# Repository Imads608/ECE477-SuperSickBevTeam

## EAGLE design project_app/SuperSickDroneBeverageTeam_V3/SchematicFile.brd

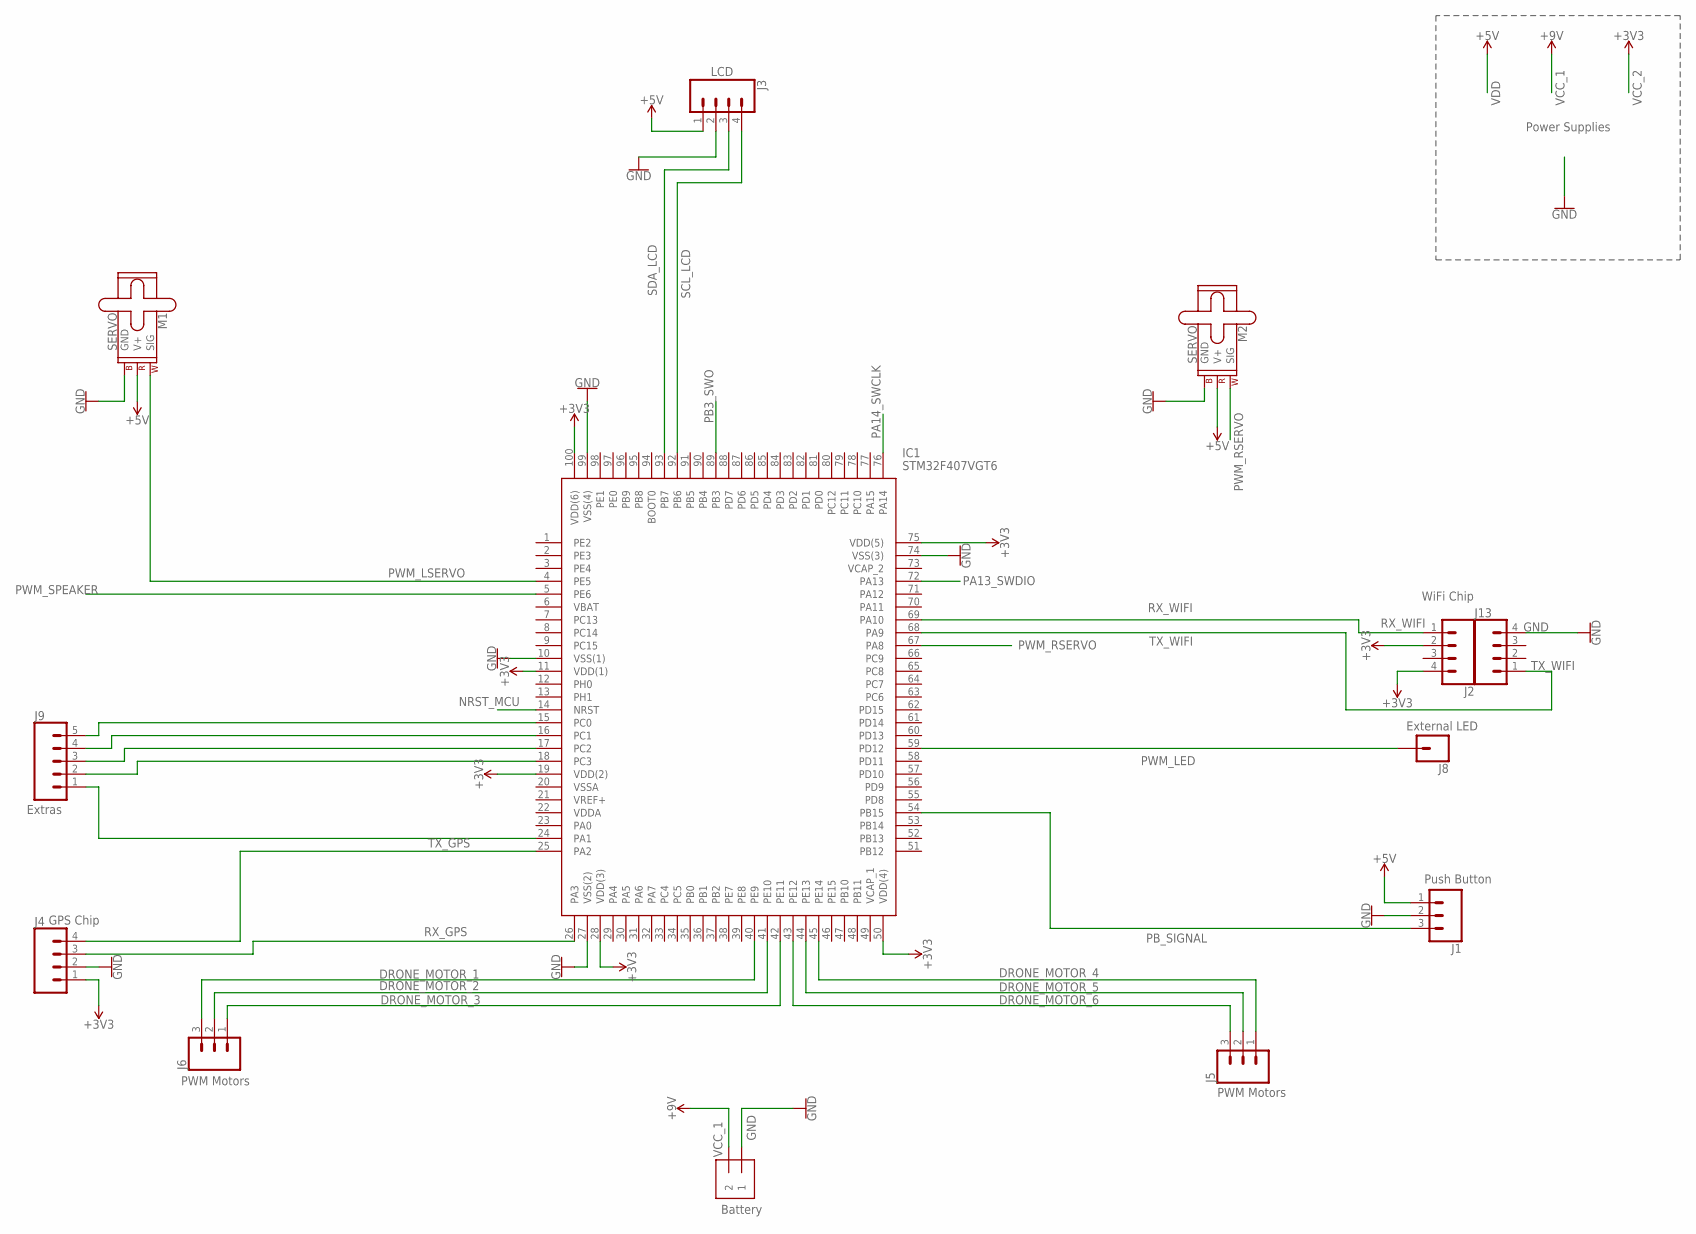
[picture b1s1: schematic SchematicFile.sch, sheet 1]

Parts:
IC1: STM32F407VGT6; QFP50P1600X1600X160-100N
J1, J5, J6: CONN_03; 1X03
J2, J3, J4, J13: CONN_04; 1X04
J8: CONN_01; 1X01
J9: CONN_05; 1X05
J11: 1X2-3.5MM
M1, M2: SERVO; 1X03

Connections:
DRONE_MOTOR_1: IC1.40 (PE9), J6.3
DRONE_MOTOR_2: IC1.41 (PE10), J6.2
DRONE_MOTOR_3: IC1.42 (PE11), J6.1
DRONE_MOTOR_4: IC1.45 (PE14), J5.1
DRONE_MOTOR_5: IC1.44 (PE13), J5.2
DRONE_MOTOR_6: IC1.43 (PE12), J5.3
GND: IC1.10 (VSS(1)), IC1.27 (VSS(2)), IC1.74 (VSS(3)), IC1.99 (VSS(4)), J1.2, J3.2, J4.2, J11.1, J13.4, M1.3 (GND), M2.3 (GND); also elsewhere on the board
NRST_MCU: IC1.14 (NRST); also elsewhere on the board
PA1_EXT: IC1.24 (PA1), J9.1
PA13_SWDIO: IC1.72 (PA13); also elsewhere on the board
PA14_SWCLK: IC1.76 (PA14); also elsewhere on the board
PB3_SWO: IC1.89 (PB3); also elsewhere on the board
PB_SIGNAL: IC1.54 (PB15), J1.3
PC0_EXT: IC1.15 (PC0), J9.5
PC1_EXT: IC1.16 (PC1), J9.4
PC2_EXT: IC1.17 (PC2), J9.3
PC3_EXT: IC1.18 (PC3), J9.2
PWM_LED: IC1.59 (PD12), J8.1
PWM_LSERVO: IC1.4 (PE5), M1.1 (SIG)
PWM_RSERVO: IC1.67 (PA8), M2.1 (SIG)
PWM_SPEAKER: IC1.5 (PE6); also elsewhere on the board
RX_GPS: IC1.26 (PA3), J4.3
RX_WIFI: IC1.69 (PA10), J2.1
SCL_LCD: IC1.92 (PB6), J3.4
SDA_LCD: IC1.93 (PB7), J3.3
TX_GPS: IC1.25 (PA2), J4.4
TX_WIFI: IC1.68 (PA9), J13.1
VCC_1: J11.2; also elsewhere on the board
VCC_2: IC1.11 (VDD(1)), IC1.19 (VDD(2)), IC1.28 (VDD(3)), IC1.50 (VDD(4)), IC1.75 (VDD(5)), IC1.100 (VDD(6)), J2.2, J2.4, J4.1; also elsewhere on the board
VDD: J1.1, J3.1, M1.2 (V+), M2.2 (V+); also elsewhere on the board

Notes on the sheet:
WiFi Chip
LCD
GPS Chip
PWM Motors
Push Button
Power Supplies
External LED
Extras
Battery

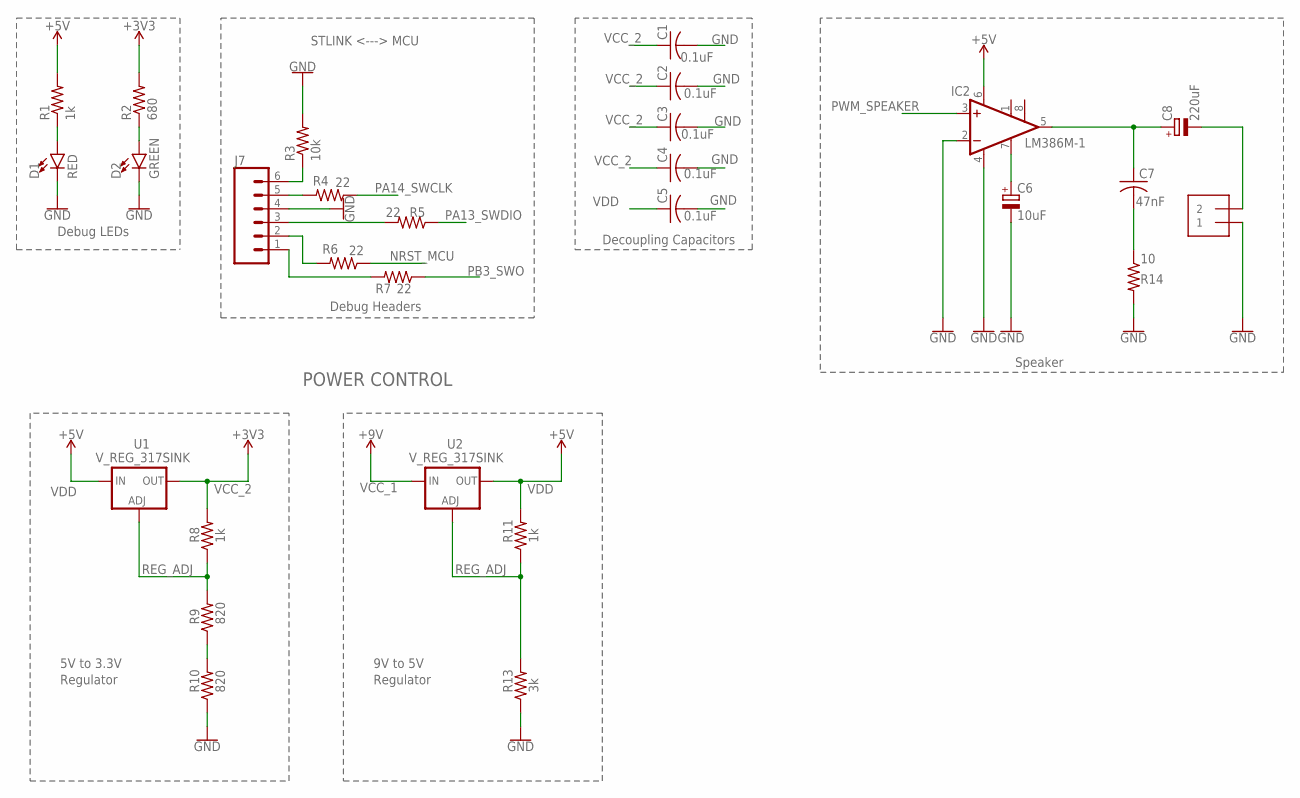
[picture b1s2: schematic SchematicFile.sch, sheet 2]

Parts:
C1, C2, C3, C4, C5: 0.1uF; C0805
C6: 10uF; E2,5-5
C7: 47nF; C0805
C8: 220uF; E2,5-5
D1: RED; LED-1206
D2: GREEN; LED-1206
IC2: LM386M-1; SO08
J7: CONN_06SILK_FEMALE_PTH; 1X06
J12: 1X2-3.5MM
R1, R8, R11: 1k; R0805
R2: 680; R0805
R3: 10k; R0805
R4, R5, R6, R7: 22; R0805
R9, R10: 820; R0805
R13: 3k; R0805
R14: 10; R0805
U1, U2: V_REG_317SINK; TO220-ADJ

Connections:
AUDIO_OUT: C8.-, J12.2
GND: C1.2, C2.2, C3.2, C4.2, C5.2, C6.-, D1.C, D2.C, IC2.2 (-IN), IC2.4 (GND), J7.4, J12.1, R3.2, R10.1, R13.1, R14.2; also elsewhere on the board
GND_STLNK: J7.6, R3.1
unnamed: D1.A, R1.1
unnamed: D2.A, R2.1
unnamed: C6.+, IC2.7 (BYPASS)
unnamed: C7.1, C8.+, IC2.5 (OUT)
unnamed: C7.2, R14.1
unnamed: R9.1, R10.2
NRST_MCU: R6.1; also elsewhere on the board
NRST_STLNK: J7.2, R6.2
PA13_SWDIO: R5.1; also elsewhere on the board
PA14_SWCLK: R4.1; also elsewhere on the board
PB3_SWO: R7.1; also elsewhere on the board
PWM_SPEAKER: IC2.3 (+IN); also elsewhere on the board
REG_ADJ: R8.1, R9.2, R11.1, R13.2, U1.ADJ, U2.ADJ
SWCLK: J7.5, R4.2
SWDIO: J7.3, R5.2
SWO: J7.1, R7.2
VCC_1: U2.IN; also elsewhere on the board
VCC_2: C1.1, C2.1, C3.1, C4.1, R2.2, R8.2, U1.OUT; also elsewhere on the board
VDD: C5.1, IC2.6 (VS), R1.2, R11.2, U1.IN, U2.OUT; also elsewhere on the board

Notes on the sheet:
Debug LEDs
Debug Headers
STLINK <---> MCU
Decoupling Capacitors
POWER CONTROL
5V to 3.3V
Regulator
9V to 5V
Speaker

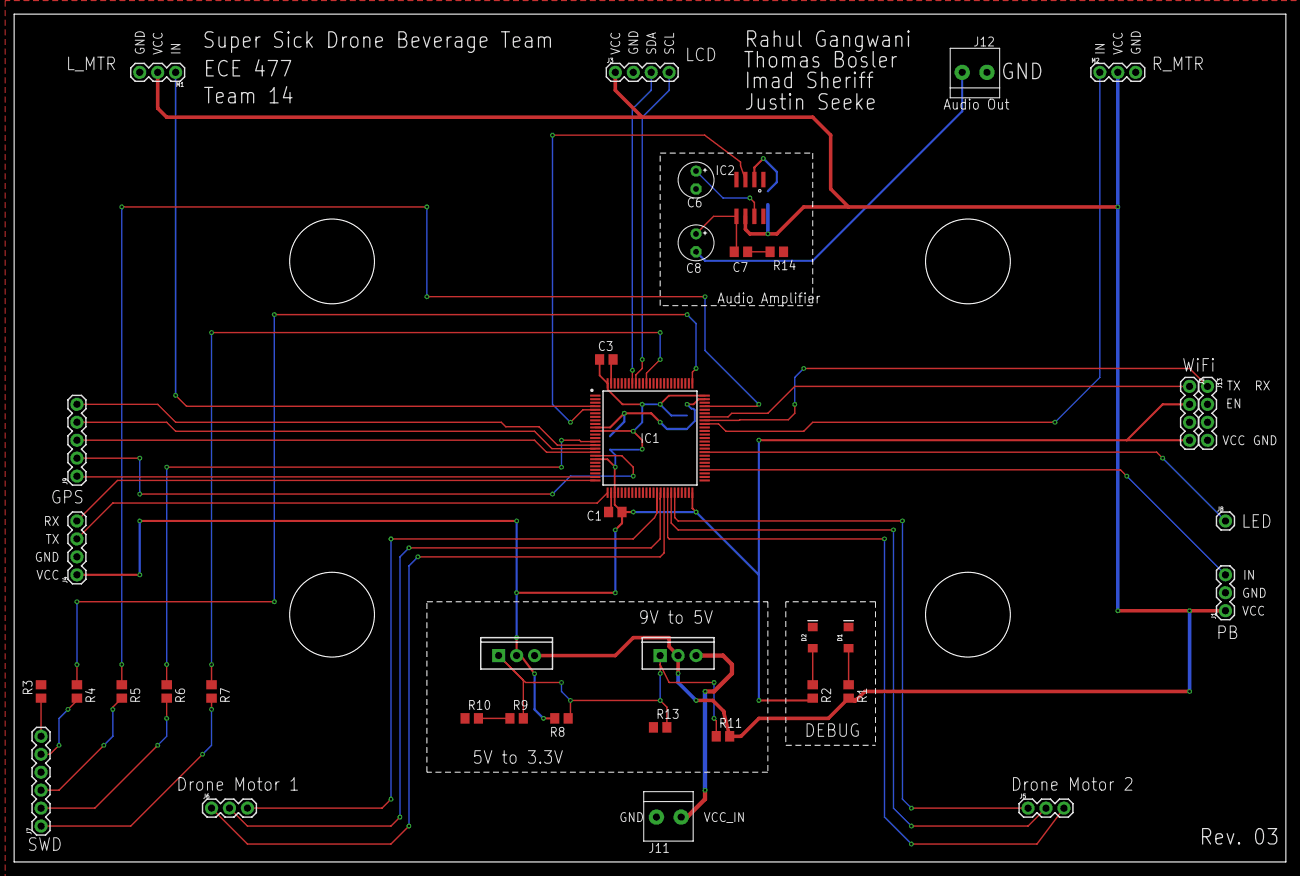
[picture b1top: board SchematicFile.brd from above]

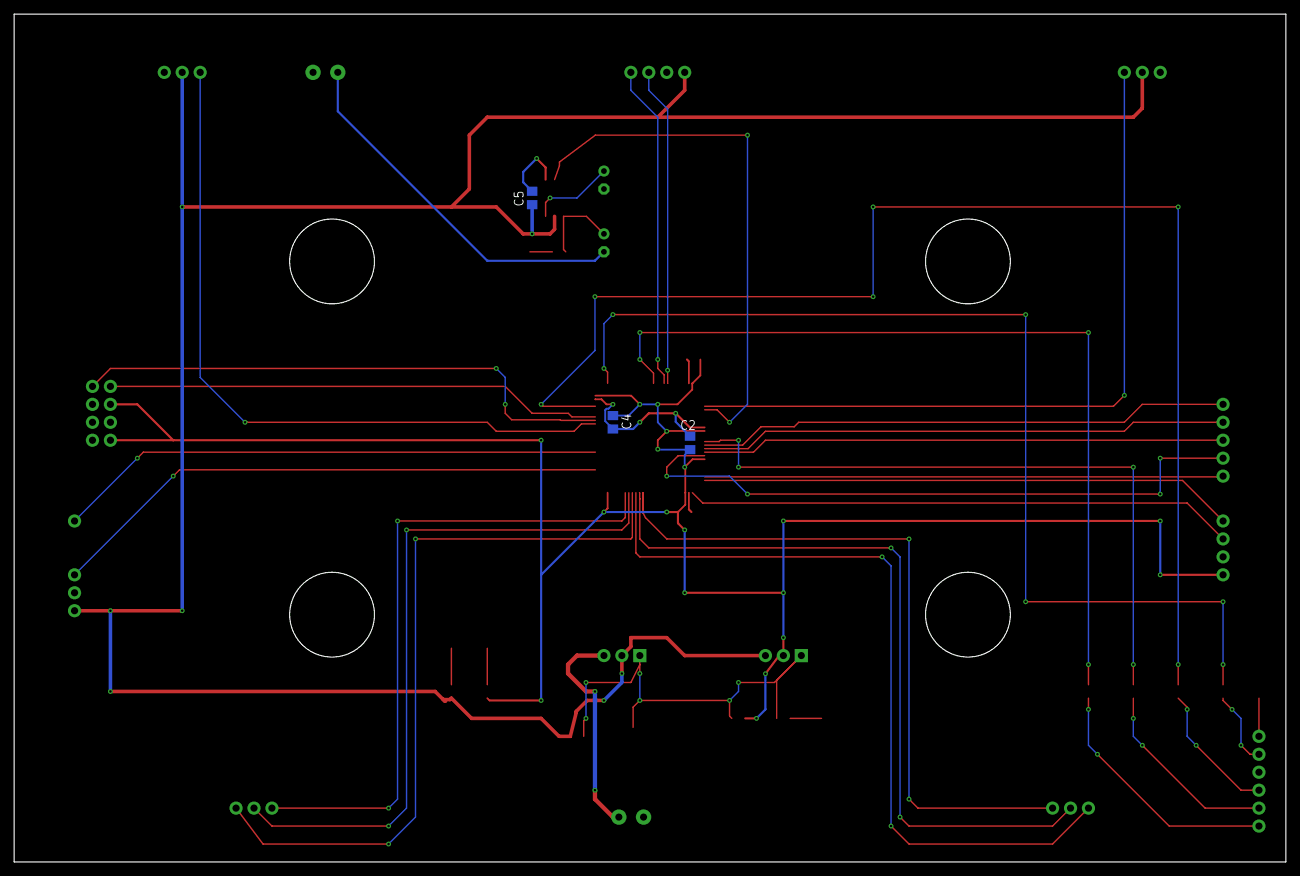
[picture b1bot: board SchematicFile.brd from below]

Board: 2 copper layers, 180.0 x 120.0 mm, 41 parts (3 on the bottom side), 43 nets.

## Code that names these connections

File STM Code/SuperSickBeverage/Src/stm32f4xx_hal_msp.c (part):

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  /* USER CODE END I2C1_MspInit 0 */
  
    /**I2C1 GPIO Configuration    
    PB6     ------> I2C1_SCL
    PB7     ------> I2C1_SDA 
    */
    GPIO_InitStruct.Pin = GPIO_PIN_6|GPIO_PIN_7;
    GPIO_InitStruct.Mode = GPIO_MODE_AF_OD;
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    __HAL_RCC_I2C1_CLK_DISABLE();
  
    /**I2C1 GPIO Configuration    
    PB6     ------> I2C1_SCL
    PB7     ------> I2C1_SDA 
    */
    HAL_GPIO_DeInit(GPIOB, GPIO_PIN_6|GPIO_PIN_7);

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
  /* USER CODE END TIM1_MspPostInit 0 */
    /**TIM1 GPIO Configuration    
    PE11     ------> TIM1_CH2
    PE13     ------> TIM1_CH3
    PE14     ------> TIM1_CH4
    PA8     ------> TIM1_CH1 
    */
    GPIO_InitStruct.Pin = GPIO_PIN_11|GPIO_PIN_13|GPIO_PIN_14;
    GPIO_InitStruct.Mode = GPIO_MODE_AF_PP;
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  /* USER CODE END TIM9_MspPostInit 0 */
  
    /**TIM9 GPIO Configuration    
    PE5     ------> TIM9_CH1
    PE6     ------> TIM9_CH2 
    */
    GPIO_InitStruct.Pin = GPIO_PIN_5|GPIO_PIN_6;
    GPIO_InitStruct.Mode = GPIO_MODE_AF_PP;
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    __HAL_RCC_USART1_CLK_ENABLE();
  
    /**USART1 GPIO Configuration    
    PA9     ------> USART1_TX
    PA10     ------> USART1_RX 
    */
    GPIO_InitStruct.Pin = GPIO_PIN_9|GPIO_PIN_10;
    GPIO_InitStruct.Mode = GPIO_MODE_AF_PP;
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    __HAL_RCC_USART2_CLK_ENABLE();
  
    /**USART2 GPIO Configuration    
    PA2     ------> USART2_TX
    PA3     ------> USART2_RX 
    */
    GPIO_InitStruct.Pin = GPIO_PIN_2|GPIO_PIN_3;
    GPIO_InitStruct.Mode = GPIO_MODE_AF_PP;
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    __HAL_RCC_USART1_CLK_DISABLE();
  
    /**USART1 GPIO Configuration    
    PA9     ------> USART1_TX
    PA10     ------> USART1_RX 
    */
    HAL_GPIO_DeInit(GPIOA, GPIO_PIN_9|GPIO_PIN_10);

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    __HAL_RCC_USART2_CLK_DISABLE();
  
    /**USART2 GPIO Configuration    
    PA2     ------> USART2_TX
    PA3     ------> USART2_RX 
    */
    HAL_GPIO_DeInit(GPIOA, GPIO_PIN_2|GPIO_PIN_3);

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
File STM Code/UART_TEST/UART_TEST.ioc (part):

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Mcu.Name=STM32F407V(E-G)Tx
Mcu.Package=LQFP100
Mcu.UserName=STM32F407VGTx
PA10.Mode=Asynchronous
PA10.Signal=USART1_RX
PA13.Mode=Serial_Wire
PA13.Signal=SYS_JTMS-SWDIO
PA14.Mode=Serial_Wire
PA14.Signal=SYS_JTCK-SWCLK
PA2.Mode=Asynchronous
PA2.Signal=USART2_TX
PA3.Mode=Asynchronous
PA3.Signal=USART2_RX
PA9.Mode=Asynchronous
PA9.Signal=USART1_TX
PB10.Mode=Asynchronous
PB10.Signal=USART3_TX
PB11.Mode=Asynchronous
PB11.Signal=USART3_RX
PB6.Mode=I2C
PB6.Signal=I2C1_SCL
PB7.Mode=I2C
PB7.Signal=I2C1_SDA
PD12.Signal=GPIO_Output
RCC.HSE_VALUE=8000000
RCC.SYSCLKFreq_VALUE=50000000
RCC.SYSCLKSource=RCC_SYSCLKSOURCE_PLLCLK
board=STM32F4DISCOVERY
boardIOC=true

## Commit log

2018-02-14 Added App files
2018-02-23 Communication Working. Need more work
2018-02-28 Done with softAP communication
2018-02-28 Added Schematic and Board Layouts
2018-04-04 Added animation for phone app. ESP code needs some more testing
2018-04-08 Uploaded additional functionality for app. Cleaned up Arduino code
2018-04-08 Added hotspot functionality to ESP
2018-04-08 Added STM and UART_TEST Code
2018-04-12 Set Socket Timeout Connection for Android App
2018-04-12 Actually added Timeout for app. Also was not up to date >.>
2018-04-13 ANOTHER ONE BITES THE DUST. Added router functionality to ESP. WOOHOO
2018-04-14 Added debug-free esp-server code
2018-04-14 UART_Test with WiFi working yay
2018-04-16 Added functionality to account for multiple clients in esp_server
2018-04-16 Added multiple clients functionality to drone app
2018-04-16 Increased array buffer in esp code to account for Mello Yello
2018-04-16 Added functionality to deal with cancelling order from micro
2018-04-19 STM code updated. PWM code moved from interrupt
2018-04-22 Hiccup with ESP WiFi reconnection. Works now with manual reconnect using in built LED
2018-04-22 Updated SuperSick Code
2018-04-24 Finalized App. (Removed Cancel Order functionality)
2018-04-24 ESP Code ready for demo with Router Config
2018-04-25 Temp commit (NOT WORKING)
2018-04-25 Updated ESP Code (Works now) Having Current Supply Issues
2018-04-25 Changed Password phrase in ESP Code
2018-04-27 pre spark code
2018-04-30 Altitude Test Code

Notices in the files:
STM Code/SuperSickBeverage/Src/stm32f4xx_hal_msp.c:
COPYRIGHT(c) 2018 STMicroelectronics
(C) COPYRIGHT STMicroelectronics *****END OF FILE
parts and their libraries:
SparkFun-Connectors: Licensing: Creative Commons ShareAlike 4.0 International - https://creativecommons.org/licenses/by-sa/4.0
